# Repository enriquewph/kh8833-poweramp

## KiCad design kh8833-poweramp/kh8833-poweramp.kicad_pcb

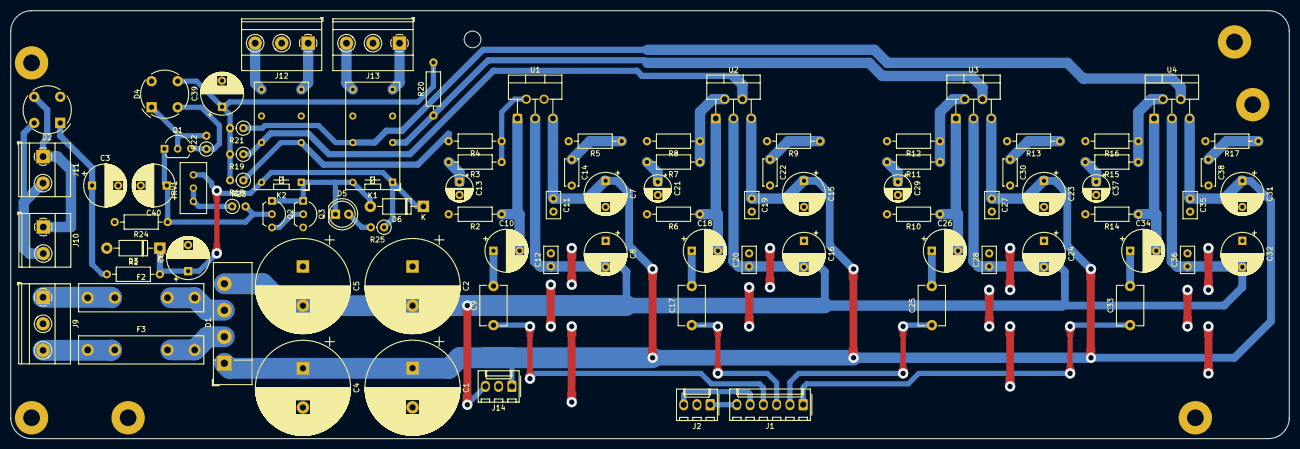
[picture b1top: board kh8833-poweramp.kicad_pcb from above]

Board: 2 copper layers, 245.0 x 82.0 mm, 91 parts (0 on the bottom side), 53 nets.

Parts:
C1, C2, C4, C5: 4700uF; CP_Radial_D18.0mm_P7.50mm
C3: 470uF; CP_Radial_D8.0mm_P5.00mm
C6, C7, C8, C15, C16, C23, C24, C31, C32, C39, C40: 220uF; CP_Radial_D8.0mm_P5.00mm
C9, C17, C25, C33: 0.22uF; C_Disc_D7.5mm_W5.0mm_P7.50mm
C10, C18, C26, C34: 1uF; CP_Radial_D8.0mm_P5.00mm
C11, C12, C19, C20, C27, C28, C35, C36: 0.1uF; C_Disc_D5.0mm_W2.5mm_P2.50mm
C13, C21, C29, C37: 22uF; CP_Radial_D5.0mm_P2.50mm
C14, C22, C30, C38: 0.1uF; C_Disc_D5.0mm_W2.5mm_P5.00mm
D1: KBU6B; Diode_Bridge_Vishay_KBU
D2, D4: D_Bridge_+-AA; Diode_Bridge_Round_D9.0mm
D3: 1N4742A; D_DO-41_SOD81_P10.16mm_Horizontal
D5: LED; LED_D5.0mm
D6: 1N4007; D_DO-41_SOD81_P10.16mm_Horizontal
F2, F3: 7.5A; Fuseholder_Littelfuse_445_030_series_5x20mm
J1: Conn_01x06; Molex_KK-254_AE-6410-06A_1x06_P2.54mm_Vertical
J2, J14: Conn_01x03; Molex_KK-254_AE-6410-03A_1x03_P2.54mm_Vertical
J9, J12, J13: Conn_01x03; TerminalBlock_Phoenix_MKDS-1,5-3-5.08_1x03_P5.08mm_Horizont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
J10, J11: Conn_01x02; TerminalBlock_Phoenix_MKDS-1,5-2-5.08_1x02_P5.08mm_Horizont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
K1, K2: HJR1-2C; Relay_DPDT_Omron_G5V-2
Q1, Q2: BC546; TO-92L_Inline_Wide
Q3: BC547; TO-92L_Inline_Wide
R1: 22; R_Axial_DIN0207_L6.3mm_D2.5mm_P10.16mm_Horizontal
R2, R6, R10, R14: 22k; R_Axial_DIN0207_L6.3mm_D2.5mm_P10.16mm_Horizontal
R3, R7, R11, R15: 680; R_Axial_DIN0207_L6.3mm_D2.5mm_P10.16mm_Horizontal
R4, R8, R12, R16: 33k; R_Axial_DIN0207_L6.3mm_D2.5mm_P10.16mm_Horizontal
R5, R9, R13, R17: 4.7; R_Axial_DIN0207_L6.3mm_D2.5mm_P10.16mm_Horizontal
R18, R19, R21, R22: 10k; R_Axial_DIN0207_L6.3mm_D2.5mm_P2.54mm_Vertical
R20: 10k; R_Axial_DIN0207_L6.3mm_D2.5mm_P10.16mm_Horizontal
R23: 10K; R_Axial_DIN0207_L6.3mm_D2.5mm_P2.54mm_Vertical
R24: 39K; R_Axial_DIN0207_L6.3mm_D2.5mm_P10.16mm_Horizontal
R25: 1k; R_Axial_DIN0207_L6.3mm_D2.5mm_P2.54mm_Vertical
RV1: 250K; Potentiometer_Bourns_3296W_Vertical
U1, U2, U3, U4: TDA2050; TO-220-5_P3.4x3.7mm_StaggerOdd_Lead3.8mm_Vertical

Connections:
+12V: C6.1, D3.1 (K), D6.1 (K), K1.1, K2.16, R1.2, R25.1, RV1.1
+24V: C1.1, C4.1, C7.1, C11.1, C15.1, C19.1, C23.1, C27.1, C31.1, C35.1, D1.1 (+), J14.1, U1.5 (+Vs), U2.5 (+Vs), U3.5 (+Vs), U4.5 (+Vs)
-24V: C2.2, C5.2, C8.2, C12.1, C16.2, C20.1, C24.2, C28.1, C32.2, C36.1, D1.4 (-), J14.3, U1.3 (-Vs), U2.3 (-Vs), U3.3 (-Vs), U4.3 (-Vs)
/Protector de Parlantes/In-1: K2.4, R4.2, R5.2, R18.1, U1.4
/Protector de Parlantes/In-2: K2.13, R8.2, R9.2, R19.1, U2.4
/Protector de Parlantes/In-3: K1.4, R12.2, R13.2, R20.1, U3.4
/Protector de Parlantes/In-4: K1.13, R16.2, R17.2, R21.1, U4.4
/Protector de Parlantes/Out-1: J12.1, K2.8
/Protector de Parlantes/Out-2: J12.3, K2.9
/Protector de Parlantes/Out-3: J13.1, K1.8
/Protector de Parlantes/Out-4: J13.3, K1.9
/TDA2050Amp0/INPUT: C9.1, J1.4
/TDA2050Amp1/INPUT: C17.1, J1.3
/TDA2050Amp2/INPUT: C25.1, J1.2
/TDA2050Amp3/INPUT: C33.1, J1.1
GND: C1.2, C2.1, C3.2, C4.2, C5.1, C6.2, C7.2, C8.1, C11.2, C12.2, C13.2, C14.2, C15.2, C16.1, C19.2, C20.2, C21.2, C22.2, C23.2, C24.1, C27.2, C28.2, C29.2, C30.2, C31.2, C32.1, C35.2, C36.2, C37.2, C38.2, C39.2, C40.2, D2.2 (-), D3.2 (A), D4.4, J2.2, J9.2, J12.2, J13.2, J14.2, Q3.3 (E), R2.2, R6.2, R10.2, R14.2, R24.2
unnamed: C3.1, D2.1 (+), R1.1
unnamed: C9.2, C10.1
unnamed: C10.2, R2.1, U1.1 (+)
unnamed: C13.1, R3.2
unnamed: C14.1, R5.1
unnamed: C17.2, C18.1
unnamed: C18.2, R6.1, U2.1 (+)
unnamed: C21.1, R7.2
unnamed: C22.1, R9.1
unnamed: C25.2, C26.1
unnamed: C26.2, R10.1, U3.1 (+)
unnamed: C29.1, R11.2
unnamed: C30.1, R13.1
unnamed: C33.2, C34.1
unnamed: C34.2, R14.1, U4.1 (+)
unnamed: C37.1, R15.2
unnamed: C38.1, R17.1
unnamed: C39.1, D4.3, R18.2, R19.2, R20.2, R21.2
unnamed: C40.1, Q1.1 (C), Q2.2 (B), R23.2, R24.1
unnamed: D1.2, F3.2
unnamed: D1.3, F2.2
unnamed: D2.3, J10.1, J11.1
unnamed: D2.4, J10.2, J11.2
unnamed: D4.1 (+), Q1.2 (B), R22.2
unnamed: D4.2 (-), Q1.3 (E), R22.1
unnamed: D5.1 (K), D6.2 (A), K1.16, K2.1, Q2.1 (C), Q3.1 (C)
unnamed: D5.2 (A), R25.2
unnamed: F2.1, J9.1
unnamed: F3.1, J9.3
unnamed: J1.5, J2.3
unnamed: J1.6, J2.1
unnamed: Q2.3 (E), Q3.2 (B)
unnamed: R3.1, R4.1, U1.2 (-)
unnamed: R7.1, R8.1, U2.2 (-)
unnamed: R11.1, R12.1, U3.2 (-)
unnamed: R15.1, R16.1, U4.2 (-)
unnamed: R23.1, RV1.2, RV1.3

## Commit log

2022-08-04 Add speaker protection
2022-08-06 Add speaker prot - v1.0
